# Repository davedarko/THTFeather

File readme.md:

## Description
I had this edgy idea to make a chunky old school Arduino thing that fits the feather form factor. USB-B port and a 3V regulator make this compatible with most featherwings, there's even the built_in LED on PIN 13 to get your blinkies starting.

## Details
This section can be used to explain everything about your project.
Can be upgraded to the Atmega328P of course, but the main goal was to have an Atmega8 DIP feather, mostly to trigger people, but the idea grew on me. Also: everyone probably has a DIP Atmega8 laying around somewhere, doing nothing - this board will give it something to do.

### more
[Hackaday Project Page](https://hackaday.io/project/171446-tht-feather-with-atmega8)

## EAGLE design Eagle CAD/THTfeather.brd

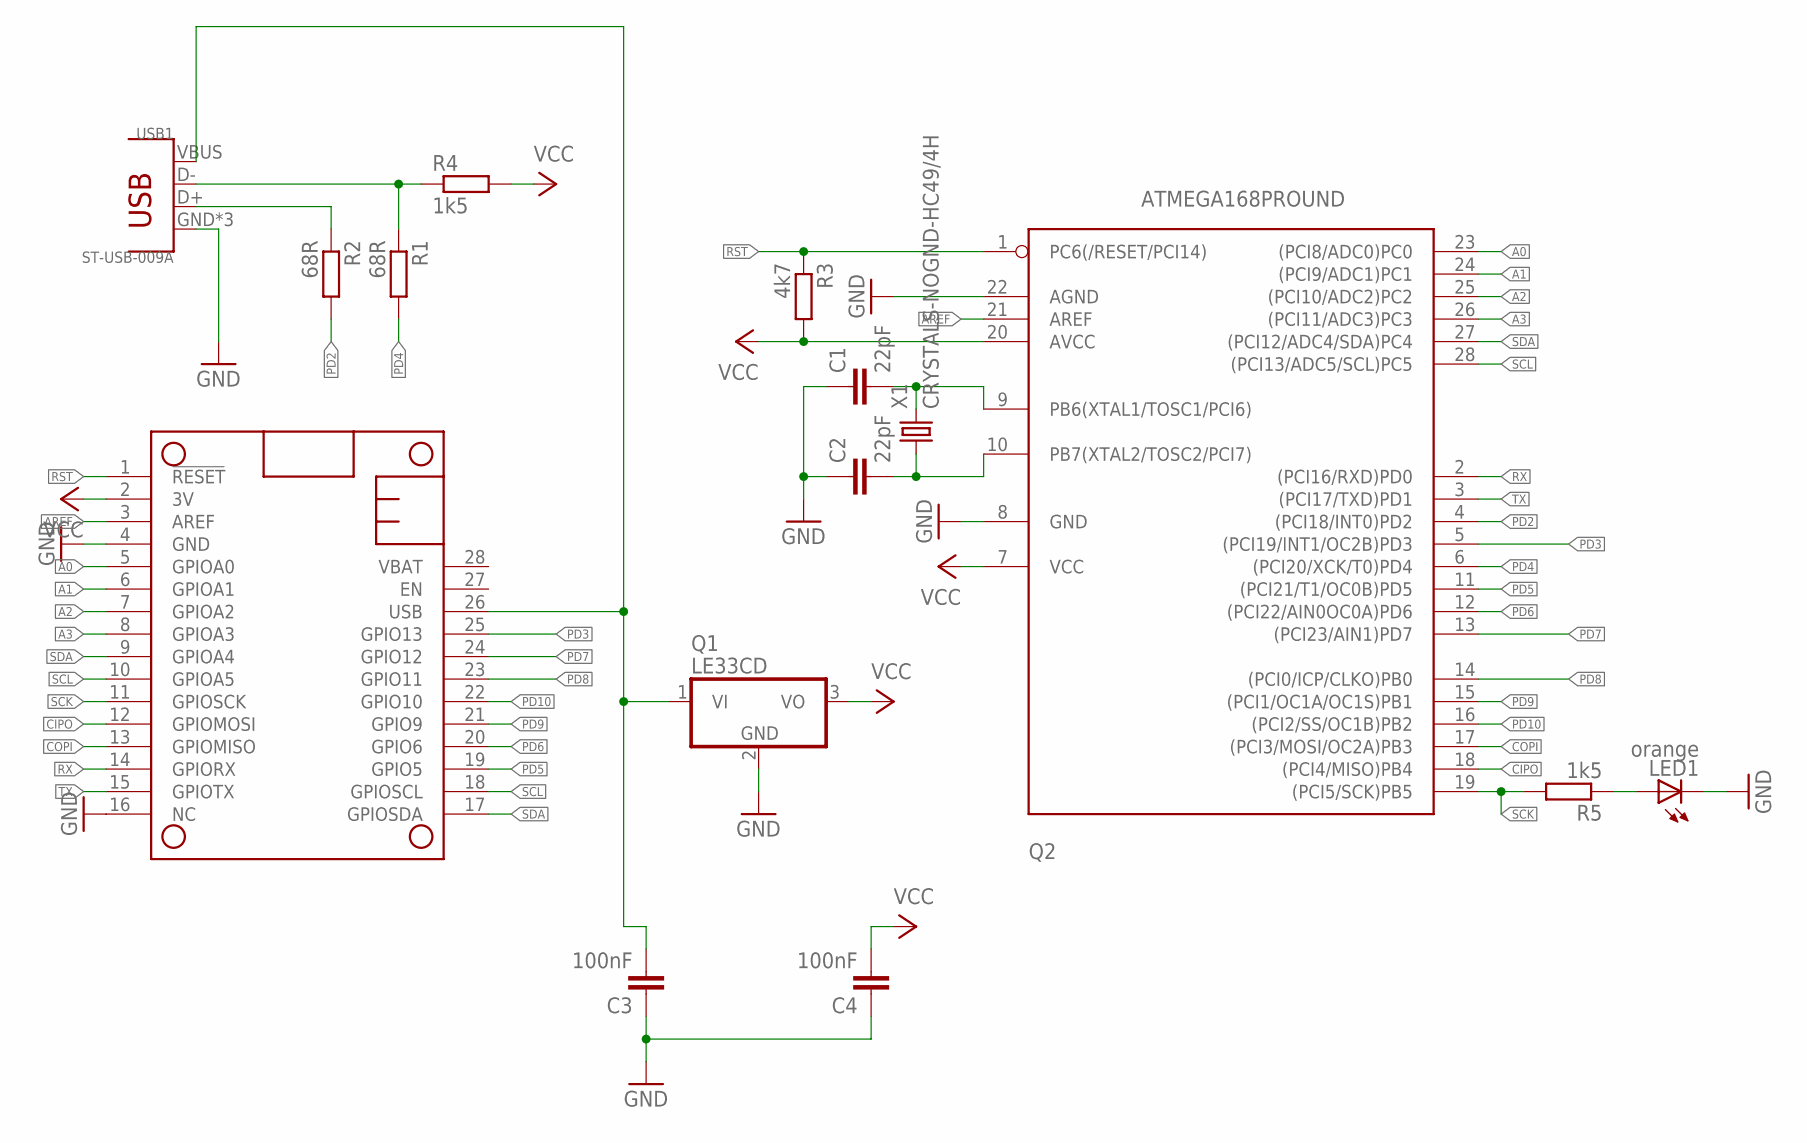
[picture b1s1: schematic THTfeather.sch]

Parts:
C1, C2: 22pF; C025-025X050
C3, C4: 100nF; C025-025X050
LED1: orange; LED3MM
MS1: FEATHERWING_NODIM; FEATHERWING_DIM
Q1: LE33CD; TO92
Q2: ATMEGA168PROUND; DIL28-3-ROUND
R1, R2: 68R; 0204/5
R3: 4k7; 0204/5
R4, R5: 1k5; 0204/5
USB1: ST-USB-009A; USB4+2-2.5-90D
X1: CRYSTALS-NOGND-HC49/4H; HC49

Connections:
A0: MS1.5 (GPIOA0), Q2.23 ((PCI8/ADC0)PC0)
A1: MS1.6 (GPIOA1), Q2.24 ((PCI9/ADC1)PC1)
A2: MS1.7 (GPIOA2), Q2.25 ((PCI10/ADC2)PC2)
A3: MS1.8 (GPIOA3), Q2.26 ((PCI11/ADC3)PC3)
AREF: MS1.3 (AREF), Q2.21 (AREF)
CIPO: MS1.12 (GPIOMOSI), Q2.18 ((PCI4/MISO)PB4)
COPI: MS1.13 (GPIOMISO), Q2.17 ((PCI3/MOSI/OC2A)PB3)
GND: C1.1, C2.1, C3.1, C4.1, LED1.K (C), MS1.4 (GND), MS1.16 (NC), Q1.2 (GND), Q2.8 (GND), Q2.22 (AGND), USB1.GND (4), USB1.S1 (4), USB1.S2 (4)
unnamed: C1.2, Q2.9 (PB6(XTAL1/TOSC1/PCI6)), X1.2
unnamed: C2.2, Q2.10 (PB7(XTAL2/TOSC2/PCI7)), X1.1
unnamed: LED1.A, R5.1
unnamed: R1.1, R4.1, USB1.D- (2)
unnamed: R2.1, USB1.D+ (3)
PD2: Q2.4 ((PCI18/INT0)PD2), R2.2
PD3: MS1.25 (GPIO13), Q2.5 ((PCI19/INT1/OC2B)PD3)
PD4: Q2.6 ((PCI20/XCK/T0)PD4), R1.2
PD5: MS1.19 (GPIO5), Q2.11 ((PCI21/T1/OC0B)PD5)
PD6: MS1.20 (GPIO6), Q2.12 ((PCI22/AIN0OC0A)PD6)
PD7: MS1.24 (GPIO12), Q2.13 ((PCI23/AIN1)PD7)
PD8: MS1.23 (GPIO11), Q2.14 ((PCI0/ICP/CLKO)PB0)
PD9: MS1.21 (GPIO9), Q2.15 ((PCI1/OC1A/OC1S)PB1)
PD10: MS1.22 (GPIO10), Q2.16 ((PCI2/SS/OC1B)PB2)
RST: MS1.1 (!RESET), Q2.1 (PC6(/RESET/PCI14)), R3.1
RX: MS1.14 (GPIORX), Q2.2 ((PCI16/RXD)PD0)
SCK: MS1.11 (GPIOSCK), Q2.19 ((PCI5/SCK)PB5), R5.2
SCL: MS1.10 (GPIOA5), MS1.18 (GPIOSCL), Q2.28 ((PCI13/ADC5/SCL)PC5)
SDA: MS1.9 (GPIOA4), MS1.17 (GPIOSDA), Q2.27 ((PCI12/ADC4/SDA)PC4)
TX: MS1.15 (GPIOTX), Q2.3 ((PCI17/TXD)PD1)
USB: C3.2, MS1.26 (USB), Q1.1 (VI), USB1.VBUS (1)
VCC: C4.2, MS1.2 (3V), Q1.3 (VO), Q2.7 (VCC), Q2.20 (AVCC), R3.2, R4.2

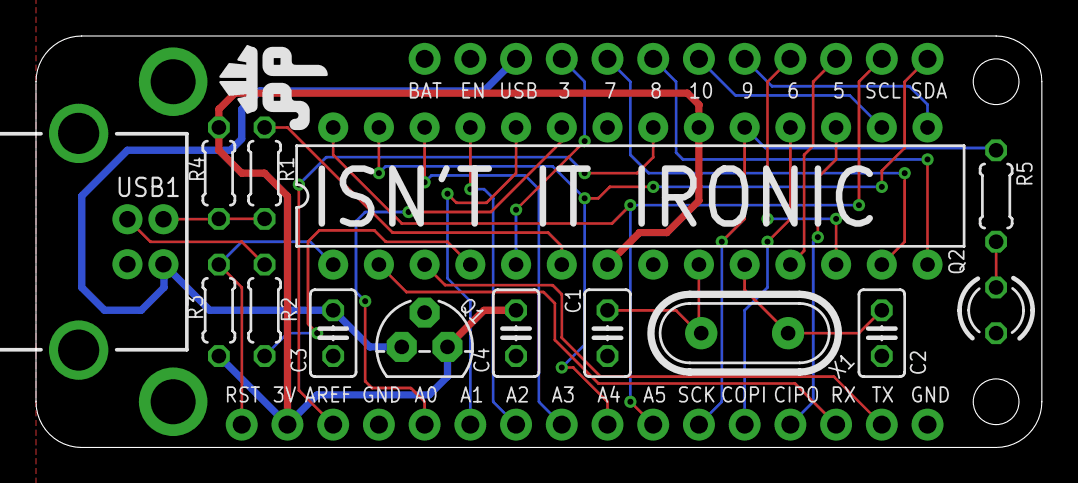
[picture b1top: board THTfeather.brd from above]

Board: 2 copper layers, 55.9 x 22.9 mm, 16 parts (0 on the bottom side), 30 nets.

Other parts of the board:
U$1: DAVEDARKO2_LOGO

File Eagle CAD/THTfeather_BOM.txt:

Partlist exported from /Users/daveploeger/code/THTFeather/Eagle CAD/THTfeather.sch at 07/07/20 23:50

Part Value                  Device                            Package         Description                MPN         VALUE      
C1   22pF                   C-EU025-025X050                   C025-025X050    CAPACITOR, European symbol                        
C2   22pF                   C-EU025-025X050                   C025-025X050    CAPACITOR, European symbol                        
C3   100nF                  C-EU025-025X050                   C025-025X050    CAPACITOR, European symbol                        
C4   100nF                  C-EU025-025X050                   C025-025X050    CAPACITOR, European symbol                        
LED1 orange                 LED3MM                            LED3MM          LED                                               
MS1  FEATHERWING_NODIM      FEATHERWING_NODIM                 FEATHERWING_DIM                                                   
Q1   LE33CD                 78L33                             TO92                                                              
Q2   ATMEGA168PROUND        ATMEGA168PROUND                   DIL28-3-ROUND   MICROCONTROLLER                                   
R1   68R                    R-EU_0204/5                       0204/5          RESISTOR, European symbol                         
R2   68R                    R-EU_0204/5                       0204/5          RESISTOR, European symbol                         
R3   4k7                    R-EU_0204/5                       0204/5          RESISTOR, European symbol                         
R4   1k5                    R-EU_0204/5                       0204/5          RESISTOR, European symbol                         
R5   1k5                    R-EU_0204/5                       0204/5          RESISTOR, European symbol                         
USB1 ST-USB-009A            DIP-USB-B-TYPE-FMAL(4+2P-2.5-90D) USB4+2-2.5-90D  320010018                  ST-USB-009A ST-USB-009A
X1   CRYSTALS-NOGND-HC49/4H CRYSTALS-NOGND-HC49/4H            HC49            CRYSTALS CAN NOT GROUNDED

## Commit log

2020-07-07 Publish
2020-07-07 read me added
